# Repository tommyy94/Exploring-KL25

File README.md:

# Plantwatch
Takes care of your precious plants.

## Table of contents

- [Description](#description)
- [Hardware](#hardware)

## Description
* Reads soil moisture, temperature and air humidity
* Waters the plant(s) according to soil moisture
* Sends data to remote database via RF link (to be implemented)
* Utilizes low power modes to save energy

## Hardware
* MKL25Z128VLK4
* nRF24L01+ radio module

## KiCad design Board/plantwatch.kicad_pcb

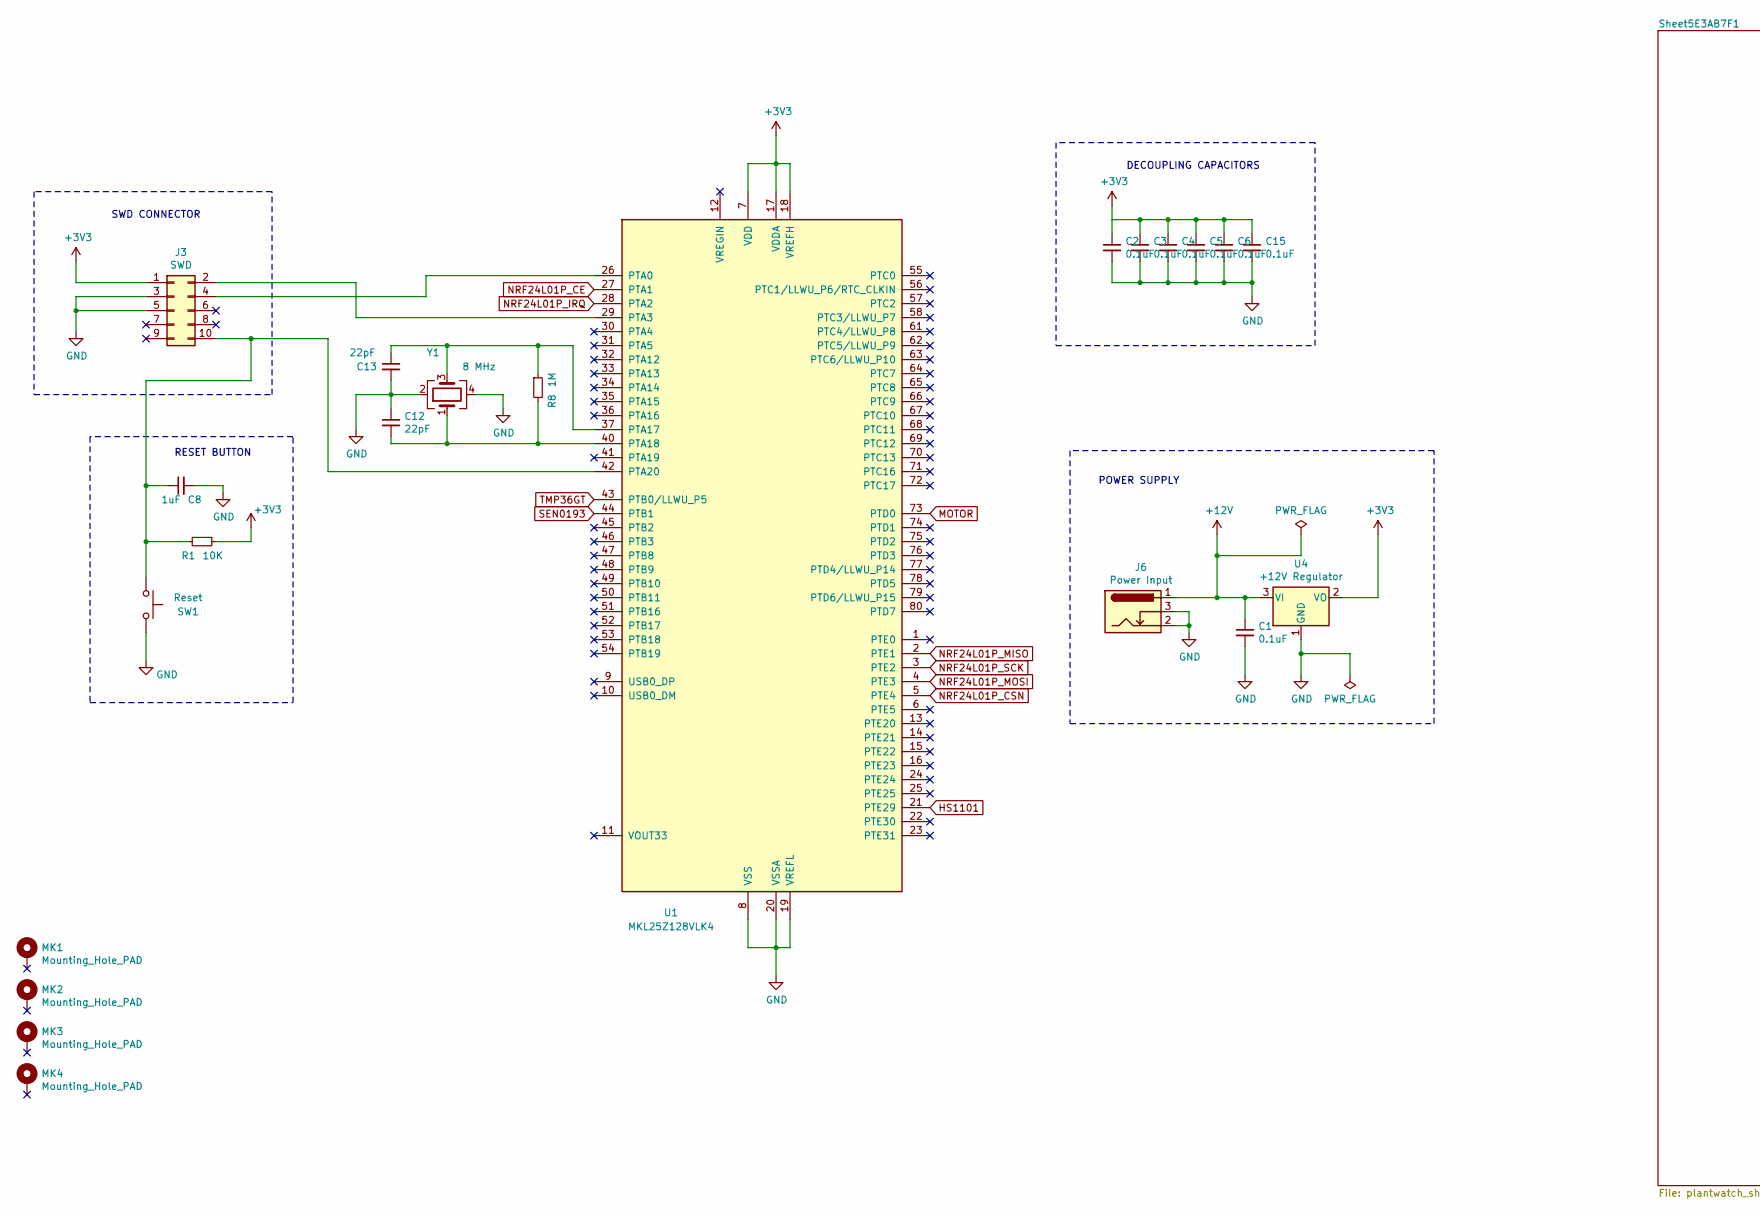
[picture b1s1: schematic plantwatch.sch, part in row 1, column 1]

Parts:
C1, C2, C3, C4, C5, C6, C15: 0.1uF; CP_EIA-3528-15_AVX-H_Pad1.50x2.35mm_HandSolder
C8: 1uF; CP_EIA-3528-15_AVX-H_Pad1.50x2.35mm_HandSolder
C12, C13: 22pF; CP_EIA-3528-15_AVX-H_Pad1.50x2.35mm_HandSolder
J3: SWD; PinHeader_2x05_P1.27mm_Vertical_SMD
J6: Power Input; BarrelJack_Horizontal
MK1, MK2, MK3, MK4: Mounting_Hole_PAD; MountingHole_2.7mm
R1: 10K; R_2512_6332Metric_Pad1.52x3.35mm_HandSolder
R8: 1M; R_2512_6332Metric_Pad1.52x3.35mm_HandSolder
SW1: Reset; SW_PUSH_6mm
U1: MKL25Z128VLK4; LQFP-80_12x12mm_P0.5mm
U4: +12V Regulator; SOT-223-3_TabPin2
Y1: 8 MHz; Crystal_SMD_0603-4Pin_6.0x3.5mm_HandSoldering

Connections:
+3V3: C2.1, C3.1, C4.1, C5.1, C6.1, C15.1, J3.1, R1.1, U1.7 (VDD), U1.17 (VDDA), U1.18 (VREFH), U1.38 (VDD), U1.60 (VDD), U4.2 (VO); also elsewhere on the board
+12V: C1.1, J6.1, U4.3 (VI); also elsewhere on the board
GND: C1.2, C2.2, C3.2, C4.2, C5.2, C6.2, C8.2, C12.1, C13.2, C15.2, J3.3, J3.5, J6.2, J6.3, SW1.2, U1.8 (VSS), U1.19 (VREFL), U1.20 (VSSA), U1.39 (VSS), U1.59 (VSS), U4.1 (GND), Y1.2, Y1.4; also elsewhere on the board
HS1101: U1.21 (PTE29); also elsewhere on the board
MOTOR: U1.73 (PTD0); also elsewhere on the board
NRF24L01P_CE: U1.27 (PTA1); also elsewhere on the board
NRF24L01P_CSN: U1.5 (PTE4); also elsewhere on the board
NRF24L01P_IRQ: U1.28 (PTA2); also elsewhere on the board
NRF24L01P_MISO: U1.2 (PTE1); also elsewhere on the board
NRF24L01P_MOSI: U1.4 (PTE3); also elsewhere on the board
NRF24L01P_SCK: U1.3 (PTE2); also elsewhere on the board
unnamed: C8.1, J3.10, R1.2, SW1.1, U1.42 (PTA20)
unnamed: C12.2, R8.2, U1.40 (PTA18), Y1.1
unnamed: C13.1, R8.1, U1.37 (PTA17), Y1.3
unnamed: J3.2, U1.29 (PTA3)
unnamed: J3.4, U1.26 (PTA0)
SEN0193: U1.44 (PTB1); also elsewhere on the board
TMP36GT: U1.43 (PTB0/LLWU_P5); also elsewhere on the board

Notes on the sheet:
RESET BUTTON
SWD CONNECTOR
POWER SUPPLY
DECOUPLING CAPACITORS

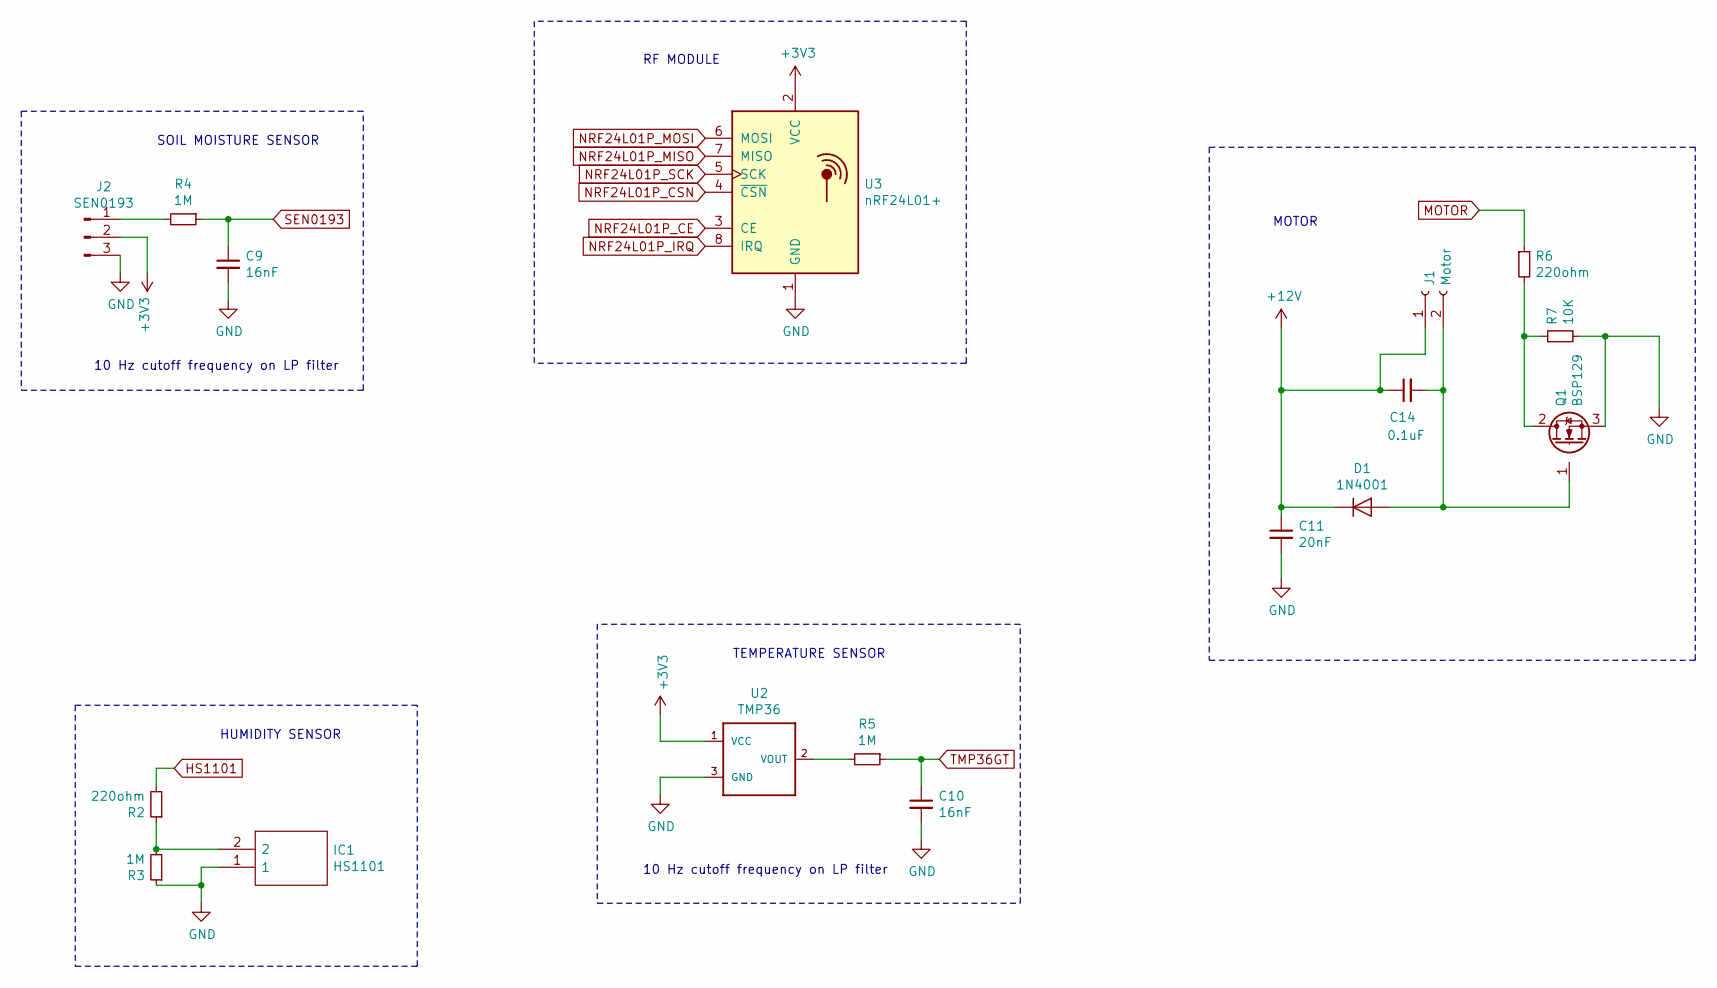
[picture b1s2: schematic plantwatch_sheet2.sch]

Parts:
C9, C10: 16nF; CP_EIA-3528-15_AVX-H_Pad1.50x2.35mm_HandSolder
C11: 20nF; CP_EIA-3528-15_AVX-H_Pad1.50x2.35mm_HandSolder
C14: 0.1uF; CP_EIA-3528-15_AVX-H_Pad1.50x2.35mm_HandSolder
D1: 1N4001; D_DO-41_SOD81_P10.16mm_Horizontal
IC1: HS1101; HS1101LF; Manufacturer_Part_Number HS1101LF; Mouser Part Number 824-HS1101LF
J1: Motor; PinSocket_2x01_P2.54mm_Vertical
J2: SEN0193; PinSocket_1x03_P2.54mm_Vertical
Q1: BSP129; SOT-223-3_TabPin2
R2, R6: 220ohm; R_2512_6332Metric_Pad1.52x3.35mm_HandSolder
R3, R4, R5: 1M; R_2512_6332Metric_Pad1.52x3.35mm_HandSolder
R7: 10K; R_2512_6332Metric_Pad1.52x3.35mm_HandSolder
U2: TMP36; TO-92
U3: nRF24L01+; nRF24L01_Breakout

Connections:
+3V3: J2.2, U2.1 (VCC), U3.2 (VCC); also elsewhere on the board
+12V: C11.1, C14.1, D1.1 (K), J1.1; also elsewhere on the board
GND: C9.2, C10.2, C11.2, IC1.1, J2.3, Q1.3 (S), R3.1, R7.2, U2.3 (GND), U3.1 (GND); also elsewhere on the board
HS1101: R2.2; also elsewhere on the board
MOTOR: R6.1; also elsewhere on the board
NRF24L01P_CE: U3.3 (CE); also elsewhere on the board
NRF24L01P_CSN: U3.4 (~CSN); also elsewhere on the board
NRF24L01P_IRQ: U3.8 (IRQ); also elsewhere on the board
NRF24L01P_MISO: U3.7 (MISO); also elsewhere on the board
NRF24L01P_MOSI: U3.6 (MOSI); also elsewhere on the board
NRF24L01P_SCK: U3.5 (SCK); also elsewhere on the board
unnamed: C14.2, D1.2 (A), J1.2, Q1.1 (G)
unnamed: IC1.2, R2.1, R3.2
unnamed: J2.1, R4.2
unnamed: Q1.2 (D), R6.2, R7.1
unnamed: R5.2, U2.2 (VOUT)
SEN0193: C9.1, R4.1; also elsewhere on the board
TMP36GT: C10.1, R5.1; also elsewhere on the board

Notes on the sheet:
HUMIDITY SENSOR
10 Hz cutoff frequency on LP filter
TEMPERATURE SENSOR
SOIL MOISTURE SENSOR
MOTOR
RF MODULE

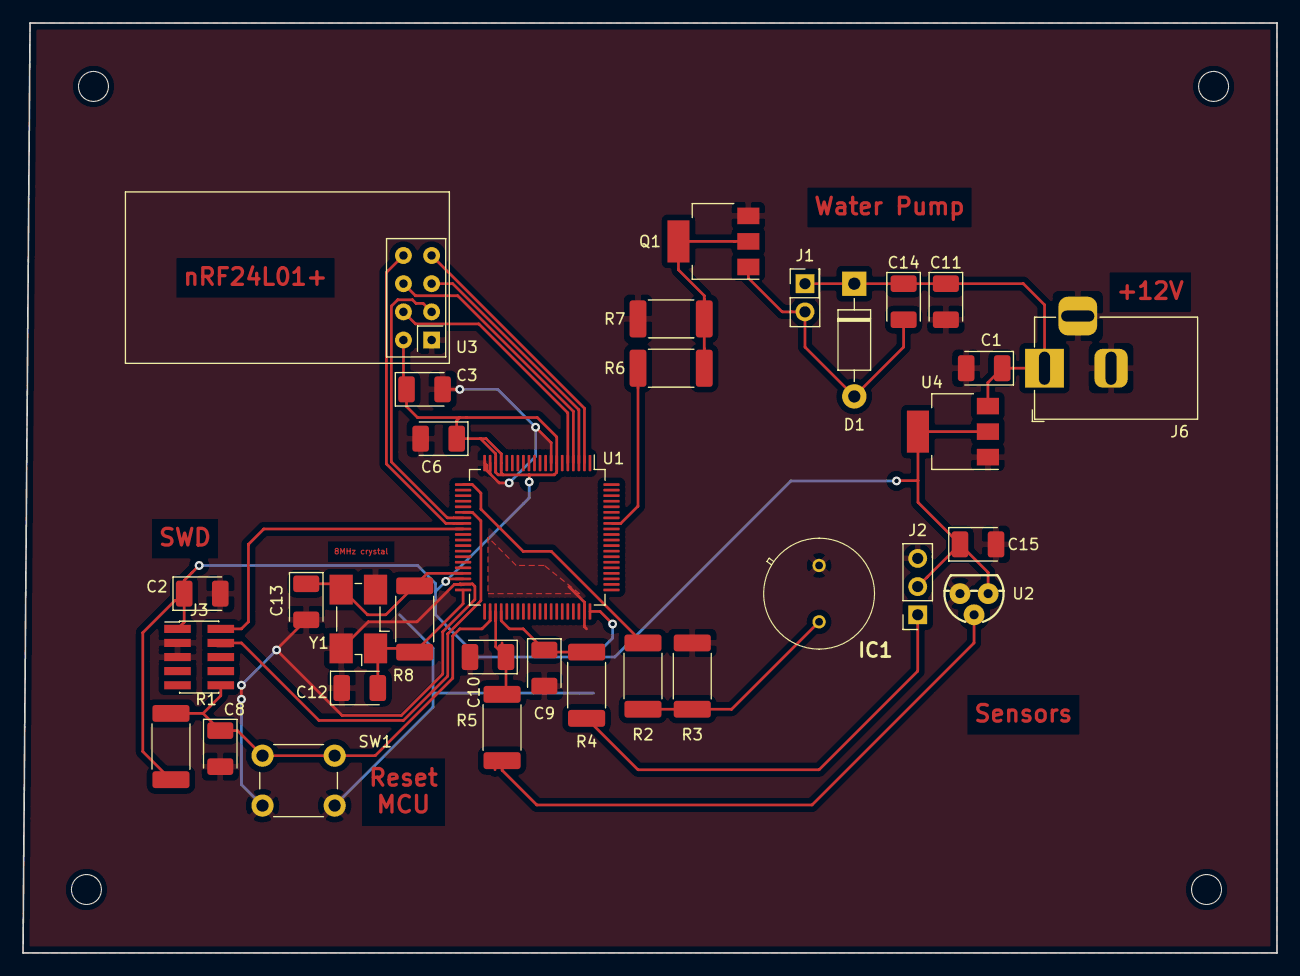
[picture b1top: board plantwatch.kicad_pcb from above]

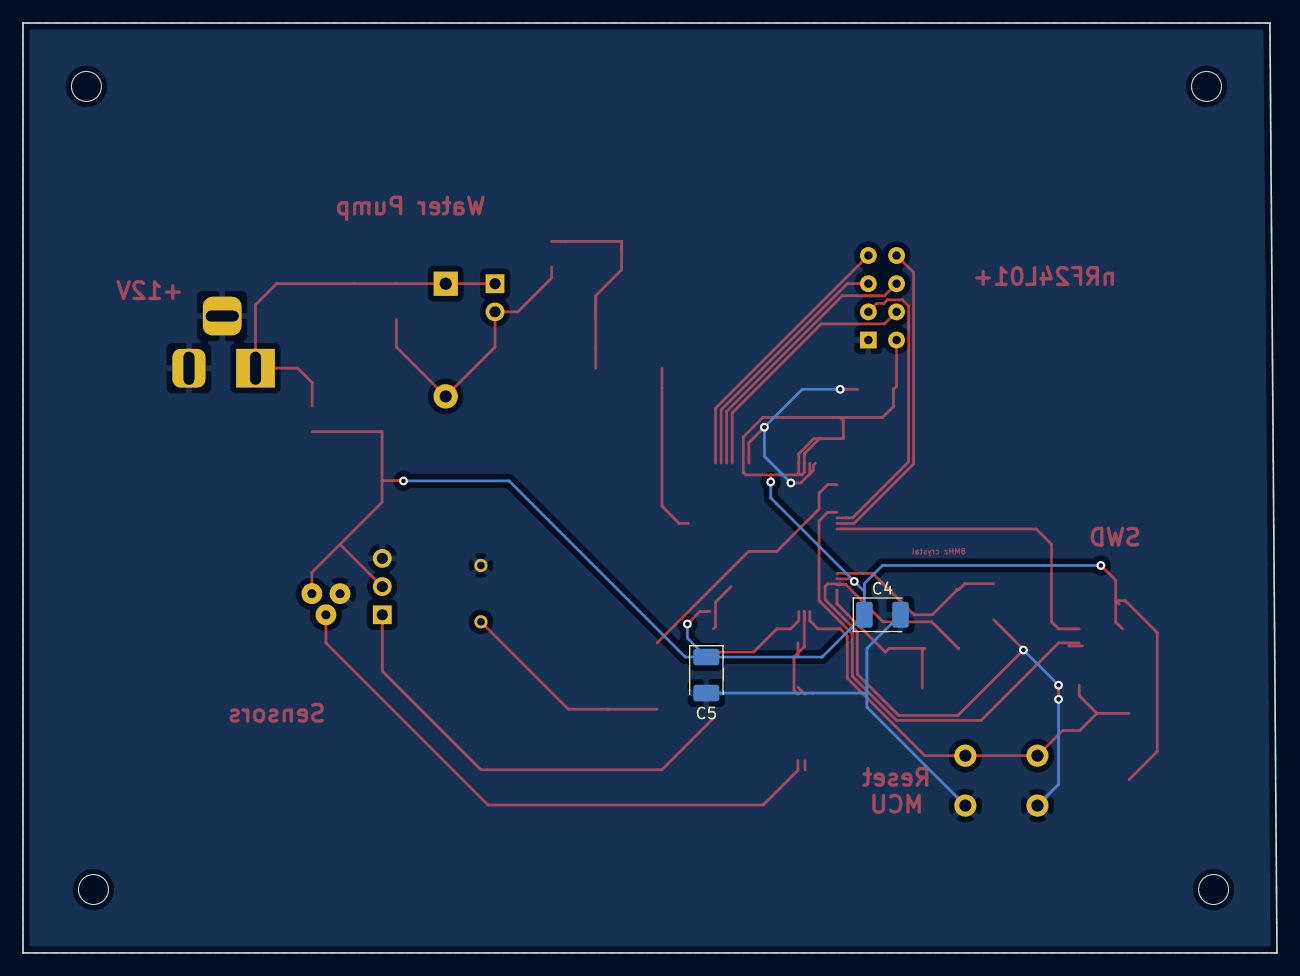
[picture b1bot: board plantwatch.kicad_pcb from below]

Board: 2 copper layers, 113.0 x 83.8 mm, 39 parts (2 on the bottom side), 23 nets.

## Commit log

2018-12-15 Project created
2018-12-19 DMA triggers only once
2019-03-27 TODO: Fix RF_SetIdleMode() TODO: Implement UART0 RX TODO: Implement CRC
2019-03-29 Add .sln file
2019-04-07 Fix TMP
2019-04-08 Fixed CMP0 trigger TMP1 is now measuring CMP0 output correctly TODO: Calibrate humidity sensor
2019-04-08 New header HS1101.h
2019-04-08 Optimized HS1101_SendSignal
2019-04-13 Fixed CMP0 noise issue with extra hysteresis (now properly reads TPM1 IC)
2019-04-13 Test project
2019-04-14 Add crc.* files
2019-04-19 Calibrated soil moisture sensor
2019-04-22 Restructured main() Built UART frame
2019-04-26 Add UART0 RX
2019-04-26 Add ack loop (not tested)
2019-04-28 Build TX frame
2019-04-29 Added FreeRTOS - work in progress
2019-05-05 Add hw_timers.*, printf-stdarg.* Fix stackoverflow caused by snprintf() (opting out of stdio.h) Qeues now working
2019-05-05 New files system.*
2019-05-05 Changed to FreeRTOS naming convention
2019-05-05 Organize source files to Inc & Src directories
2019-05-05 Add documentation
2019-05-06 Add Motor task & PWM
2019-05-06 Add FreeRTOS software timers for motor control
2019-05-07 Add events for software timers and motor control
2019-05-08 Fix motor events
2019-05-10 Fix Hard Fault by reorganizing task priorities
2019-05-10 Fix vSensorTask memory issues
2019-05-10 Add Doxygen documentation
2019-05-11 Add configASSERT() macro
2019-05-11 Add asserts for sensors and software timers
2019-05-17 Add more asserts Can now drive all motors with PWM
2019-05-17 Refactor code TPM1_IRQHandler now uses task notification instead of global variables
2019-05-17 Move README.md to project root
2019-05-17 Remove unnecessary files
2019-05-18 Fix vTimerCallback assert
2019-05-18 Add xCommSemaphore
2019-05-25 Migrate from RF module to ESP8266 Wi-Fi module
2019-05-29 CRC->SQL
2019-06-02 Add vStartupTask() Add timeout for ESP8266_vSendCmd
2019-06-09 Add BME to HW timers & DMA
2019-06-10 Comment DMA0_vInit()
2019-06-10 Add vApplicationIdleHook()
2019-06-10 Add FreeRTOS tickless idle mode (SysTick)
2019-06-29 Add TODO
    Implement remote web server
    Create PCB
2019-08-15 Move peripheral related functions to their own modules
2019-08-15 Refactoring Test SPI1
2019-08-26 SPI transfer now occurs via DMA channel 0
2019-08-27 DMA0 IRQ now triggers only once per transaction
2019-08-27 Add Ozone/ and VIsualGDB/ to .gitignore
2019-08-27 Add nrf24l01.*
2019-08-27 nRF24L01 now responds to status polling
2019-08-27 Refactor code
2019-08-28 Modify VisualGDB project files
2019-08-28 Remove todo
2019-08-28 Move DMA0_IRQHandler to comm.c Inline small functions
2019-08-28 Refactor code Remove SPI1_vSetSlave() from SPI1_vTransmitDMA()
2019-08-28 Add working implementation of nRF24L01_vWriteRegister() Modify nRF24L01_ucReadRegister()
2019-08-28 Add DMA0_IRQHandler() Add vWaitUntilTransferCplt()
2019-08-28 Remove unnecessary includes
2019-08-28 Modify VisualGDB settings
2019-08-29 Remove uart.*
2019-08-29 Fix comment
2019-08-29 Change task priorities Edit global constant names
2019-08-30 Move TPM1_IRQHandler from motor.c to sensors.c
2019-08-30 Add TPM2
2019-08-30 Remove interrupt on complete Add length parameter to DMA0_vInitTransaction()
2019-08-30 Add TPM2 Add TPM2_IRQHandler
2019-08-30 Modify baud rate
2019-08-30 Rename global constant
2019-08-30 Modify project files
2019-08-30 TPM2_vLoadCounter() now calculates delay correctly
2019-08-30 Modify debug settings
2019-08-30 Edit README.md
2019-08-30 nRF24L01 read/write register now works
2019-08-30 Add init section for nRF24L01
2019-08-31 Add nRF24L01_vWriteAddressRegister()
2019-08-31 Fix register masks
2019-08-31 Add more init section
2019-09-09 Fix nRF24L01_vSendPayload()
2019-10-08 Remove gpio.*
2019-10-08 uint8_t -> uint32_t
2019-10-08 Update nRF24L01
2019-10-20 Fix nRF24L01 transmission issue
2019-10-24 Disable asserts in Release configuration
2019-10-24 Remove useless parameter
2019-10-24 Remove useless parameter and xTimeoutEventGroup
2019-10-24 Rename project files
2019-10-25 Rename files
2019-10-26 Add working SPI implementation
2020-01-09 Clean project
2020-01-19 Fix HS1101 initialization port
2020-01-23 Add KiCad project
2020-01-24 Make layout
2020-02-05 PCB almost done
2020-02-05 Adding copper pous
2020-02-07 PCB done
2020-03-25 SWD connector footprint pitch 1.0mm -> 1.27mm
2020-03-25 Remove backup files
